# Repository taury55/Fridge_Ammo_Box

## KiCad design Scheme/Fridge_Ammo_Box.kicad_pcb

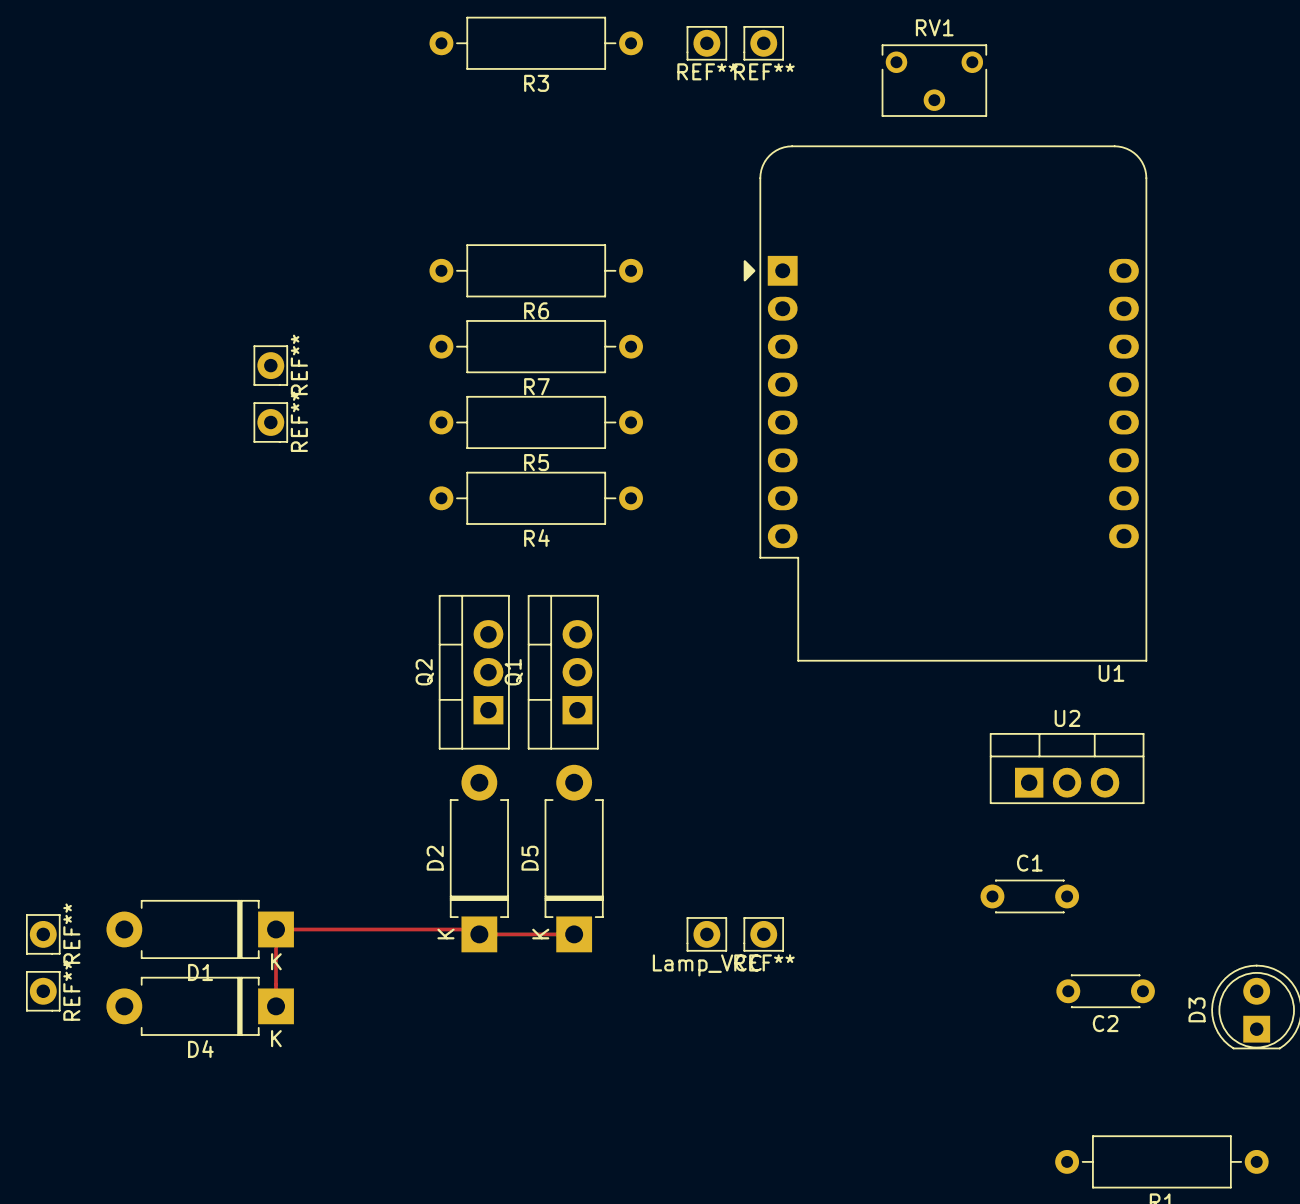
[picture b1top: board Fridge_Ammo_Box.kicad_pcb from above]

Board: 2 copper layers, 19 parts (0 on the bottom side), 13 nets.

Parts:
C1: 10nF; C_Disc_D4.3mm_W1.9mm_P5.00mm
C2: 100nF; C_Disc_D4.3mm_W1.9mm_P5.00mm
D1, D2, D4, D5: 1N5401; D_DO-15_P10.16mm_Horizontal
D3: LED; LED_D5.0mm
Lamp_VCC: Pin_D0.9mm_L10.0mm_W2.4mm_FlatFork
Q1, Q2: Q_NMOS_GDS; TO-220-3_Vertical
R1: 220ohm; R_Axial_DIN0309_L9.0mm_D3.2mm_P12.70mm_Horizontal
R3: 10k; R_Axial_DIN0309_L9.0mm_D3.2mm_P12.70mm_Horizontal
R4, R6: 100k; R_Axial_DIN0309_L9.0mm_D3.2mm_P12.70mm_Horizontal
R5, R7: 100ohm; R_Axial_DIN0309_L9.0mm_D3.2mm_P12.70mm_Horizontal
RV1: Trim 10k; Potentiometer_Bourns_3266W_Vertical
U1: WeMos_D1_mini; WEMOS_D1_mini_light
U2: L7805; TO-220-3_Vertical

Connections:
GND: C1.2, C2.2, Q1.3, Q2.3, R1.2, R3.2, R4.2, R6.2, RV1.3, U1.10, U2.2
Lamp_GND: D5.2, Q2.2
Lamp_VCC: C1.1, D1.1, D2.1, D4.1, D5.1, U2.1
unnamed: C2.1, D3.2, U1.9, U2.3
unnamed: D3.1, R1.1
unnamed: D4.2, Q1.2
unnamed: Q1.1, R5.2
unnamed: Q2.1, R7.2
unnamed: R3.1, U1.2
unnamed: R4.1, R5.1, U1.5
unnamed: R6.1, R7.1, U1.3
unnamed: RV1.2, U1.4
VCC: D1.2, D2.2
